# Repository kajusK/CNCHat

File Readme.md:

# LinuxCNC Shield for OrangePi

This repo contains a HW design files for OrangePi CNC shield for making the
OrangePi a LinuxCNC machine.

The [allwincnc](https://allwincnc.github.io/) project can be used to do the
realtime heavy lifting (stepper control) while the OrangePi does the slower
tasks (kinematics calculations,...).

More details about making this all work with a real CNC machine can be found
on [my blog](https://deadbadger.cz/projects/linuxcnc-on-orangepi)

## Features
* 5 stepper controllers (direction and step signals) supported
* 3 encoders inputs
* Spindle control - both PWM and 0-10 V outputs
* 6 limit switches (endstops, home position,...)
* Probe sensor input
* Stop button input
* 2 power outputs (cooling, ESTOP,...), up to 24 V
* Incidator leds on inputs and outputs for easier debugging
* Up to 15 V inputs protection
* Selectable 3.3/5 V power for limit switches
* OrangePi can be powered directly from the board (dedicated 5 V input) and vice versa.

## Connectors
### J21 Steppers
| Pin | Signal |
|-----|--------|
| 1 | GND |
| 2 | ~Enable |
| 3 | Y2 dir |
| 4 | Y2 step |
| 5 | X2 dir |
| 6 | X2 step |
| 7 | Z dir |
| 8 | Z step |
| 9 | Y dir |
| 10 | Y step |
| 11 | X dir |
| 12 | X step |

### J15 spindle
| Pin | Signal |
|-----|--------|
| 1 | GND |
| 2 | 0-10 V |
| 3 | PWM |

### J11, J12, J13 Encoders
| Pin | Signal |
|-----|--------|
| 1 | GND |
| 2 | B |
| 3 | A |
| 4 | 5 V |

### J1-J7 Inputs
| Pin | Signal |
|-----|--------|
| 1 | 5/3.3 V |
| 2 | GND |
| 3 | signal (with pull-up) |

## OrangePi Pinout

### Steppers
|      | X    | Y    | Z    | X2   | Y2   |
| :--  | :--: | :--: | :--: | :--: | :--: |
| Step | PA0  | PA12 | PA13 | PC4  | PA14 |
| Dir  | PA6  | PA1  | PA11 | PD14 | PC7  |

### Encoders
|      | X    | Y    | Z    |
| :--  | :--: | :--: | :--: |
| A    | PA8  | PA18 | PC2  |
| B    | PA9  | PG9  | PA21 |

### Limit switches
| Xmin | Ymin | Zmin | X2min| Y2min| Limits |
| :--: | :--: | :--: | :--: | :--: | :--:   |
| PA2  | PC1  | PA19 | PA7  | PG8  | PC3    |

### Others
| Enable | Spindle | Cooling | Probe | ESTOP in | ESTOP out |
| :--: | :--: | :--: | :--: | :--: | :--:   |
| PA3  | PC0  | PG7 | PA10  | PA20  | PG6   |

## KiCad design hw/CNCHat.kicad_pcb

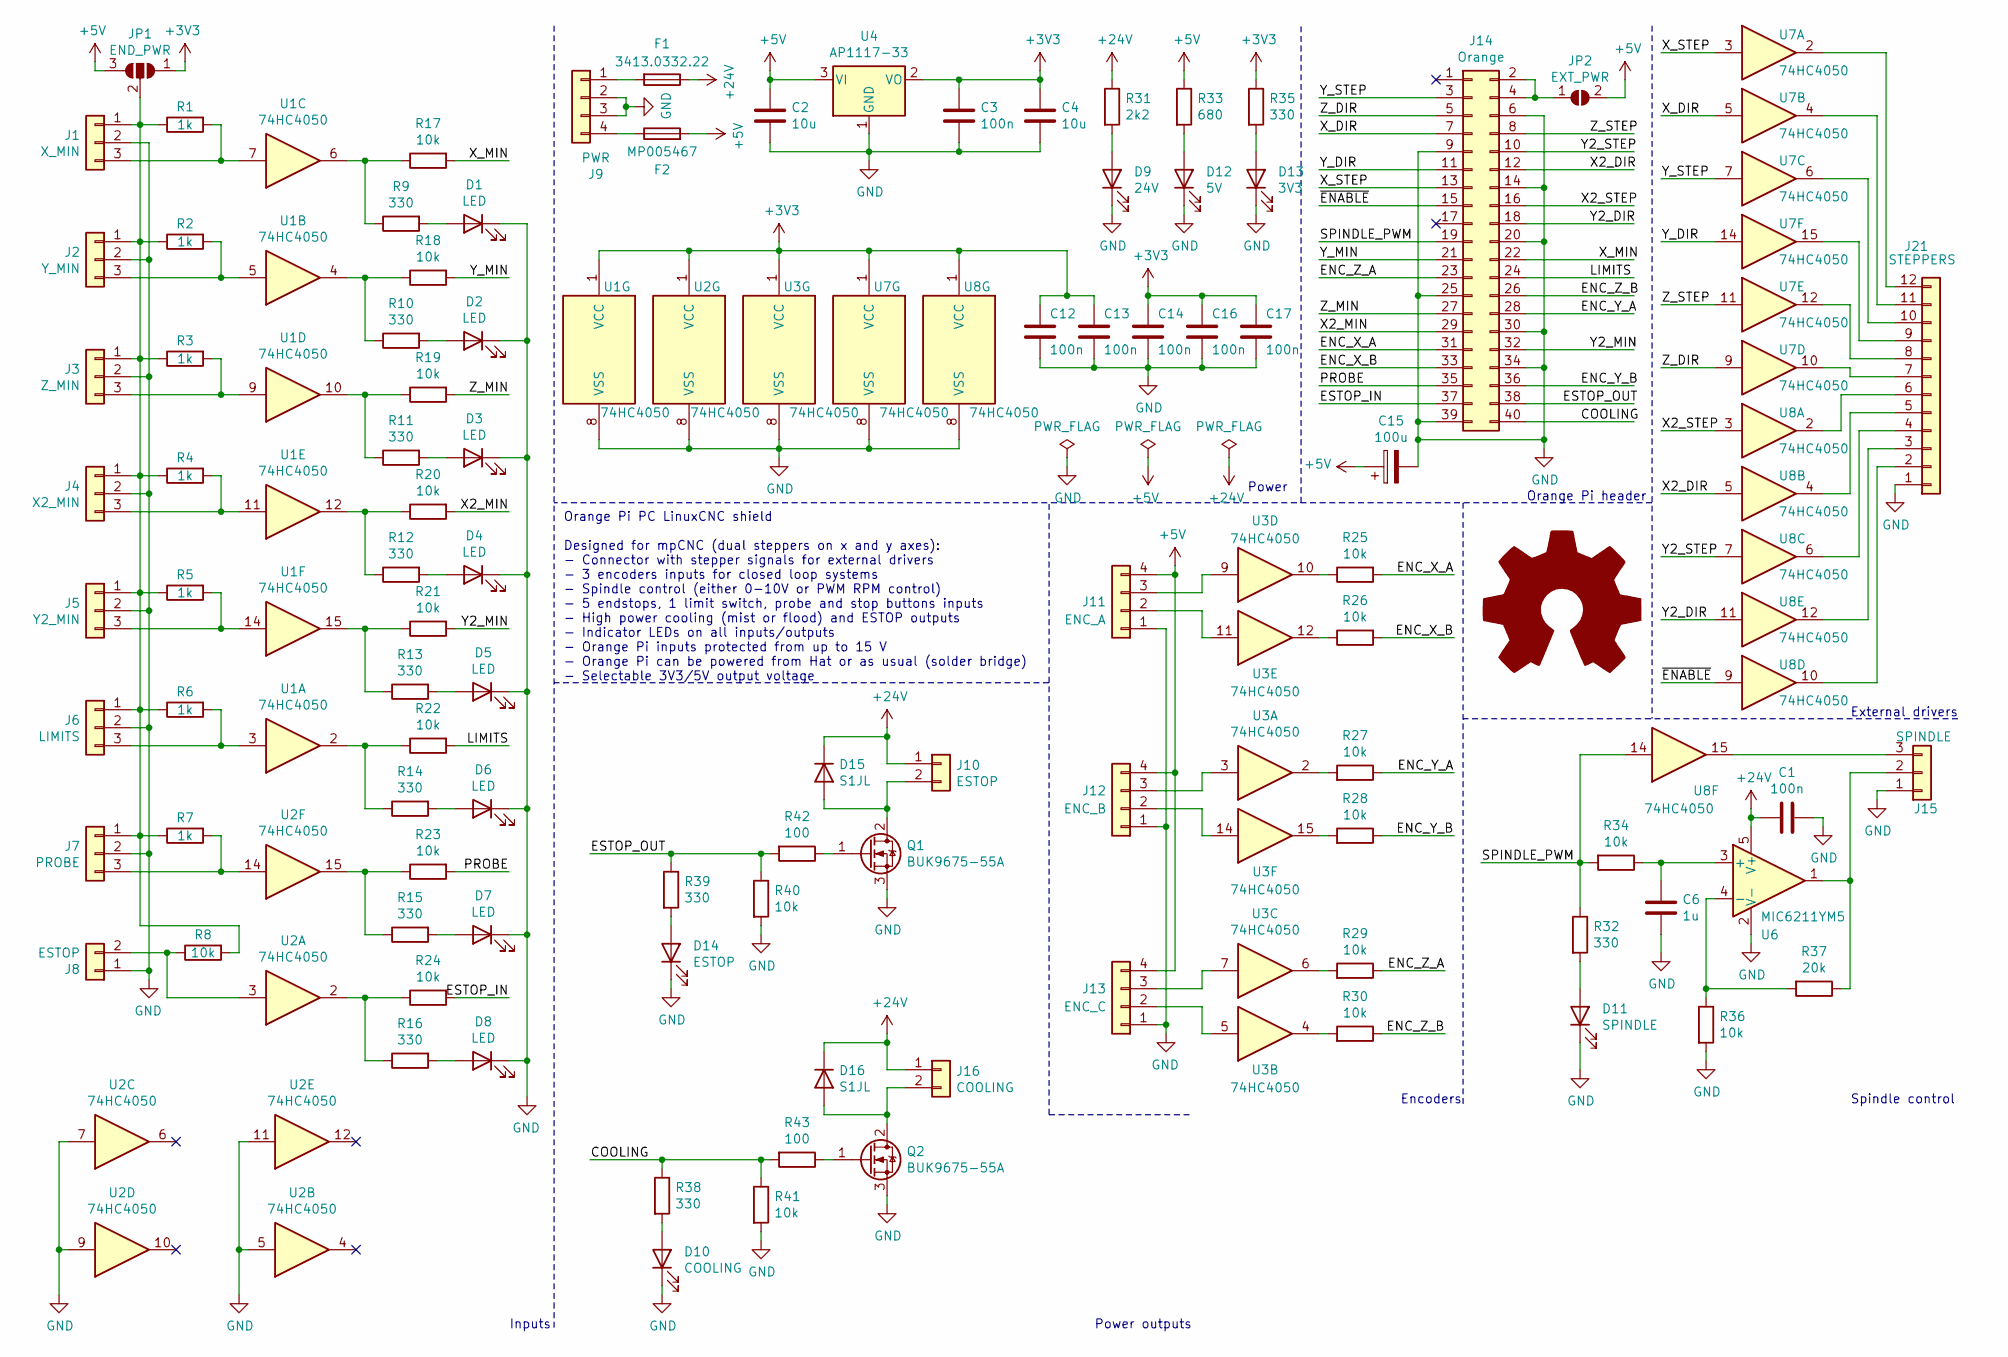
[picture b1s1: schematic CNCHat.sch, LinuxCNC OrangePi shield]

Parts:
C1, C3, C12, C13, C14, C16, C17: 100n; C_0603_1608Metric
C2, C4: 10u; C_0603_1608Metric
C6: 1u; C_0603_1608Metric
C15: 100u; CP_Elec_8x10.5
D1, D2, D3, D4, D5, D6, D7, D8: LED; LED_1206_3216Metric
D9: 24V; LED_1206_3216Metric
D10: COOLING; LED_1206_3216Metric
D11: SPINDLE; LED_1206_3216Metric
D12: 5V; LED_1206_3216Metric
D13: 3V3; LED_1206_3216Metric
D14: ESTOP; LED_1206_3216Metric
D15, D16: S1JL; D_SMA
F1: 3413.0332.22; Fuse_1206_3216Metric
F2: MP005467; Fuse_1206_3216Metric
J1: X_MIN; JST_XH_B3B-XH-A_1x03_P2.50mm_Vertical
J2: Y_MIN; JST_XH_B3B-XH-A_1x03_P2.50mm_Vertical
J3: Z_MIN; JST_XH_B3B-XH-A_1x03_P2.50mm_Vertical
J4: X2_MIN; JST_XH_B3B-XH-A_1x03_P2.50mm_Vertical
J5: Y2_MIN; JST_XH_B3B-XH-A_1x03_P2.50mm_Vertical
J6: LIMITS; JST_XH_B3B-XH-A_1x03_P2.50mm_Vertical
J7: PROBE; JST_XH_B3B-XH-A_1x03_P2.50mm_Vertical
J8: ESTOP; JST_XH_B2B-XH-A_1x02_P2.50mm_Vertical
J9: PWR; PhoenixContact_MCV_1,5_4-G-3.5_1x04_P3.50mm_Vertical
J10: ESTOP; PhoenixContact_MCV_1,5_2-G-3.5_1x02_P3.50mm_Vertical
J11: ENC_A; JST_XH_B4B-XH-A_1x04_P2.50mm_Vertical
J12: ENC_B; JST_XH_B4B-XH-A_1x04_P2.50mm_Vertical
J13: ENC_C; JST_XH_B4B-XH-A_1x04_P2.50mm_Vertical
J14: Orange; PinSocket_2x20_P2.54mm_Vertical
J15: SPINDLE; JST_XH_B3B-XH-A_1x03_P2.50mm_Vertical
J16: COOLING; PhoenixContact_MCV_1,5_2-G-3.5_1x02_P3.50mm_Vertical
J21: STEPPERS; JST_XH_B12B-XH-A_1x12_P2.50mm_Vertical
JP1: END_PWR; SolderJumper-3_P2.0mm_Open_TrianglePad1.0x1.5mm_NumberLabels
JP2: EXT_PWR; SolderJumper-2_P1.3mm_Open_TrianglePad1.0x1.5mm
Q1, Q2: BUK9675-55A; TO-263-2
R1, R2, R3, R4, R5, R6, R7: 1k; R_0603_1608Metric
R8, R17, R18, R19, R20, R21, R22, R23, R24, R25, R26, R27, R28, R29, R30, R34, R36, R40, R41: 10k; R_0603_1608Metric
R9, R10, R11, R12, R13, R14, R15, R16, R32, R35, R38, R39: 330; R_0603_1608Metric
R31: 2k2; R_0603_1608Metric
R33: 680; R_0603_1608Metric
R37: 20k; R_0603_1608Metric
R42, R43: 100; R_0603_1608Metric
U1, U2, U3, U7, U8: 74HC4050; SOIC-16_3.9x9.9mm_P1.27mm
U4: AP1117-33; SOT-223-3_TabPin2
U6: MIC6211YM5; SOT-23-5

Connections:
+3V3: C3.1, C4.1, C12.1, C13.1, C14.1, C16.1, C17.1, JP1.1 (A), R35.1, U1.1 (VCC), U2.1 (VCC), U3.1 (VCC), U4.2 (VO), U7.1 (VCC), U8.1 (VCC)
+5V: C2.1, C15.1, F2.2, J11.4, J12.4, J13.4, JP1.3 (B), JP2.2 (B), R33.1, U4.3 (VI)
+24V: C1.2, D15.1 (K), D16.1 (K), F1.1, J10.1, J16.1, R31.1, U6.5 (V+)
/COOLING: J14.40, R38.1, R41.1, R43.2
/ENC_X_A: J14.31, R25.2
/ENC_X_B: J14.33, R26.2
/ENC_Y_A: J14.28, R27.1
/ENC_Y_B: J14.36, R28.1
/ENC_Z_A: J14.23, R29.1
/ENC_Z_B: J14.26, R30.1
/ESTOP_IN: J14.37, R24.2
/ESTOP_OUT: J14.38, R39.1, R40.1, R42.2
/LIMITS: J14.24, R22.2
/PROBE: J14.35, R23.2
/SPINDLE_PWM: J14.19, R32.1, R34.2, U8.14
/X2_DIR: J14.12, U8.5
/X2_MIN: J14.29, R20.2
/X2_STEP: J14.16, U8.3
/X_DIR: J14.7, U7.5
/X_MIN: J14.22, R17.2
/X_STEP: J14.13, U7.3
/Y2_DIR: J14.18, U8.11
/Y2_MIN: J14.32, R21.2
/Y2_STEP: J14.10, U8.7
/Y_DIR: J14.11, U7.14
/Y_MIN: J14.21, R18.2
/Y_STEP: J14.3, U7.7
/Z_DIR: J14.5, U7.9
/Z_MIN: J14.27, R19.2
/Z_STEP: J14.8, U7.11
/~ENABLE: J14.15, U8.9
GND: C1.1, C2.2, C3.2, C4.2, C6.2, C12.2, C13.2, C14.2, C15.2, C16.2, C17.2, D1.1 (K), D2.1 (K), D3.1 (K), D4.1 (K), D5.1 (K), D6.1 (K), D7.1 (K), D8.1 (K), D9.1 (K), D10.1 (K), D11.1 (K), D12.1 (K), D13.1 (K), D14.1 (K), J1.2, J2.2, J3.2, J4.2, J5.2, J6.2, J7.2, J8.1, J9.2, J9.3, J11.1, J12.1, J13.1, J14.6, J14.9, J14.14, J14.20, J14.25, J14.30, J14.34, J14.39, J15.1, J21.1, Q1.3 (S), Q2.3 (S), R36.2, R40.2, R41.2, U1.8 (VSS), U2.5, U2.7, U2.8 (VSS), U2.9, U2.11, U3.8 (VSS), U4.1 (GND), U6.2 (V-), U7.8 (VSS), U8.8 (VSS)
unnamed: C6.1, R34.1, U6.3 (+)
unnamed: D1.2 (A), R9.2
unnamed: D2.2 (A), R10.2
unnamed: D3.2 (A), R11.2
unnamed: D4.2 (A), R12.2
unnamed: D5.2 (A), R13.2
unnamed: D6.2 (A), R14.2
unnamed: D7.2 (A), R15.2
unnamed: D8.2 (A), R16.2
unnamed: D9.2 (A), R31.2
unnamed: D10.2 (A), R38.2
unnamed: D11.2 (A), R32.2
unnamed: D12.2 (A), R33.2
unnamed: D13.2 (A), R35.2
unnamed: D14.2 (A), R39.2
unnamed: D15.2 (A), J10.2, Q1.2 (D)
unnamed: D16.2 (A), J16.2, Q2.2 (D)
unnamed: F1.2, J9.1
unnamed: F2.1, J9.4
unnamed: J1.1, J2.1, J3.1, J4.1, J5.1, J6.1, J7.1, JP1.2 (C), R1.1, R2.1, R3.1, R4.1, R5.1, R6.1, R7.1, R8.2
unnamed: J1.3, R1.2, U1.7
unnamed: J2.3, R2.2, U1.5
unnamed: J3.3, R3.2, U1.9
unnamed: J4.3, R4.2, U1.11
unnamed: J5.3, R5.2, U1.14
unnamed: J6.3, R6.2, U1.3
unnamed: J7.3, R7.2, U2.14
unnamed: J8.2, R8.1, U2.3
unnamed: J11.2, U3.11
unnamed: J11.3, U3.9
unnamed: J12.2, U3.14
unnamed: J12.3, U3.3
unnamed: J13.2, U3.5
unnamed: J13.3, U3.7
unnamed: J14.2, J14.4, JP2.1 (A)
unnamed: J15.2, R37.1, U6.1
unnamed: J15.3, U8.15
unnamed: J21.2, U8.10
unnamed: J21.3, U8.12
unnamed: J21.4, U8.6
unnamed: J21.5, U8.4
unnamed: J21.6, U8.2
unnamed: J21.7, U7.10
unnamed: J21.8, U7.12
unnamed: J21.9, U7.15
unnamed: J21.10, U7.6
unnamed: J21.11, U7.4
unnamed: J21.12, U7.2
unnamed: Q1.1 (G), R42.1
unnamed: Q2.1 (G), R43.1
unnamed: R10.1, R18.1, U1.4
unnamed: R11.1, R19.1, U1.10
unnamed: R12.1, R20.1, U1.12
unnamed: R13.1, R21.1, U1.15
unnamed: R14.1, R22.1, U1.2
unnamed: R15.1, R23.1, U2.15
unnamed: R16.1, R24.1, U2.2
unnamed: R9.1, R17.1, U1.6
unnamed: R25.1, U3.10
unnamed: R26.1, U3.12
unnamed: R27.2, U3.2
unnamed: R28.2, U3.15
unnamed: R29.2, U3.6
unnamed: R30.2, U3.4
unnamed: R36.1, R37.2, U6.4 (-)

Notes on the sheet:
Inputs
Encoders
External drivers
Orange Pi header
Spindle control
Orange Pi PC LinuxCNC shield Designed for mpCNC (dual steppers on x and y axes): - Connector with stepper signals for external drivers - 3 encoders inputs for closed loop systems - Spindle control (either 0-10V or PWM RPM control) - 5 endstops, 1 limit switch, probe and stop buttons inputs - High p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
Power
Power outputs

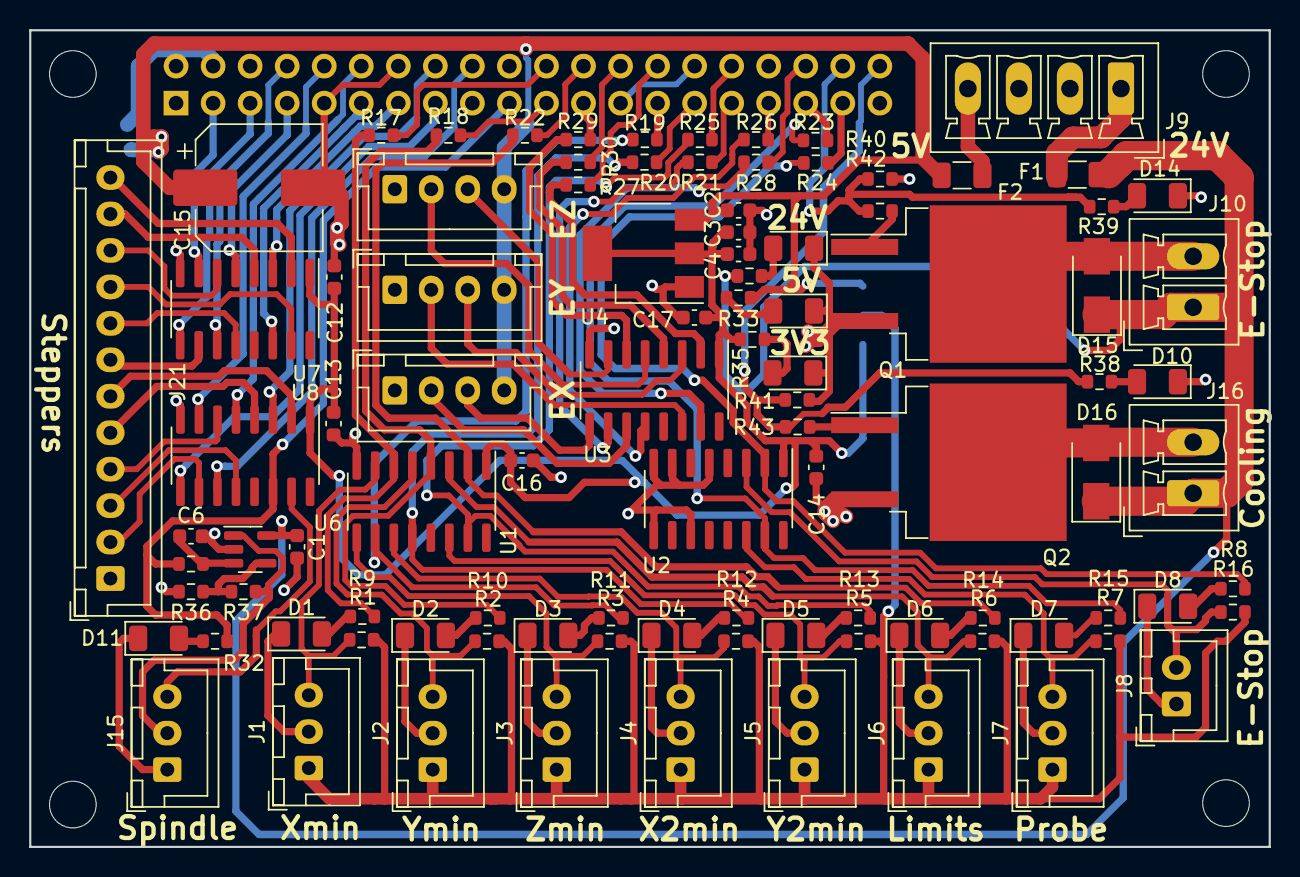
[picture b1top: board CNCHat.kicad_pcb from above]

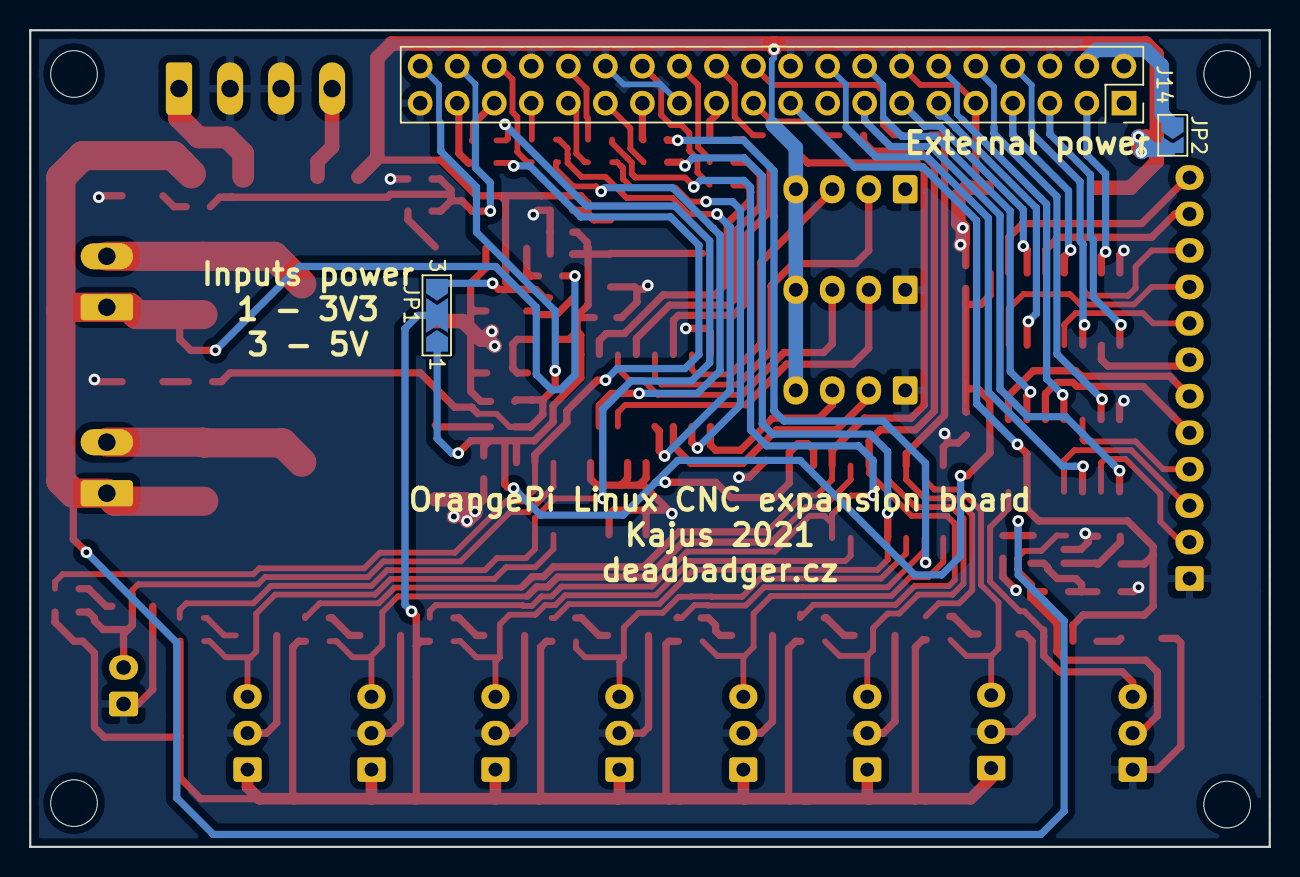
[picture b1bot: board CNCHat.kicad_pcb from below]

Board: 2 copper layers, 85.0 x 56.0 mm, 100 parts (3 on the bottom side), 97 nets.

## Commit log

2021-07-26 Initial commit, finished PCB design
2022-02-13 Added gerber files for manufacturing
2022-02-13 Added readme and schematic
2023-12-21 Added schematic in PDF
